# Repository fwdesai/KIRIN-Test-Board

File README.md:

Test board for the KIRIN hardware accelerator which was developed by Bo Wun Cheng.

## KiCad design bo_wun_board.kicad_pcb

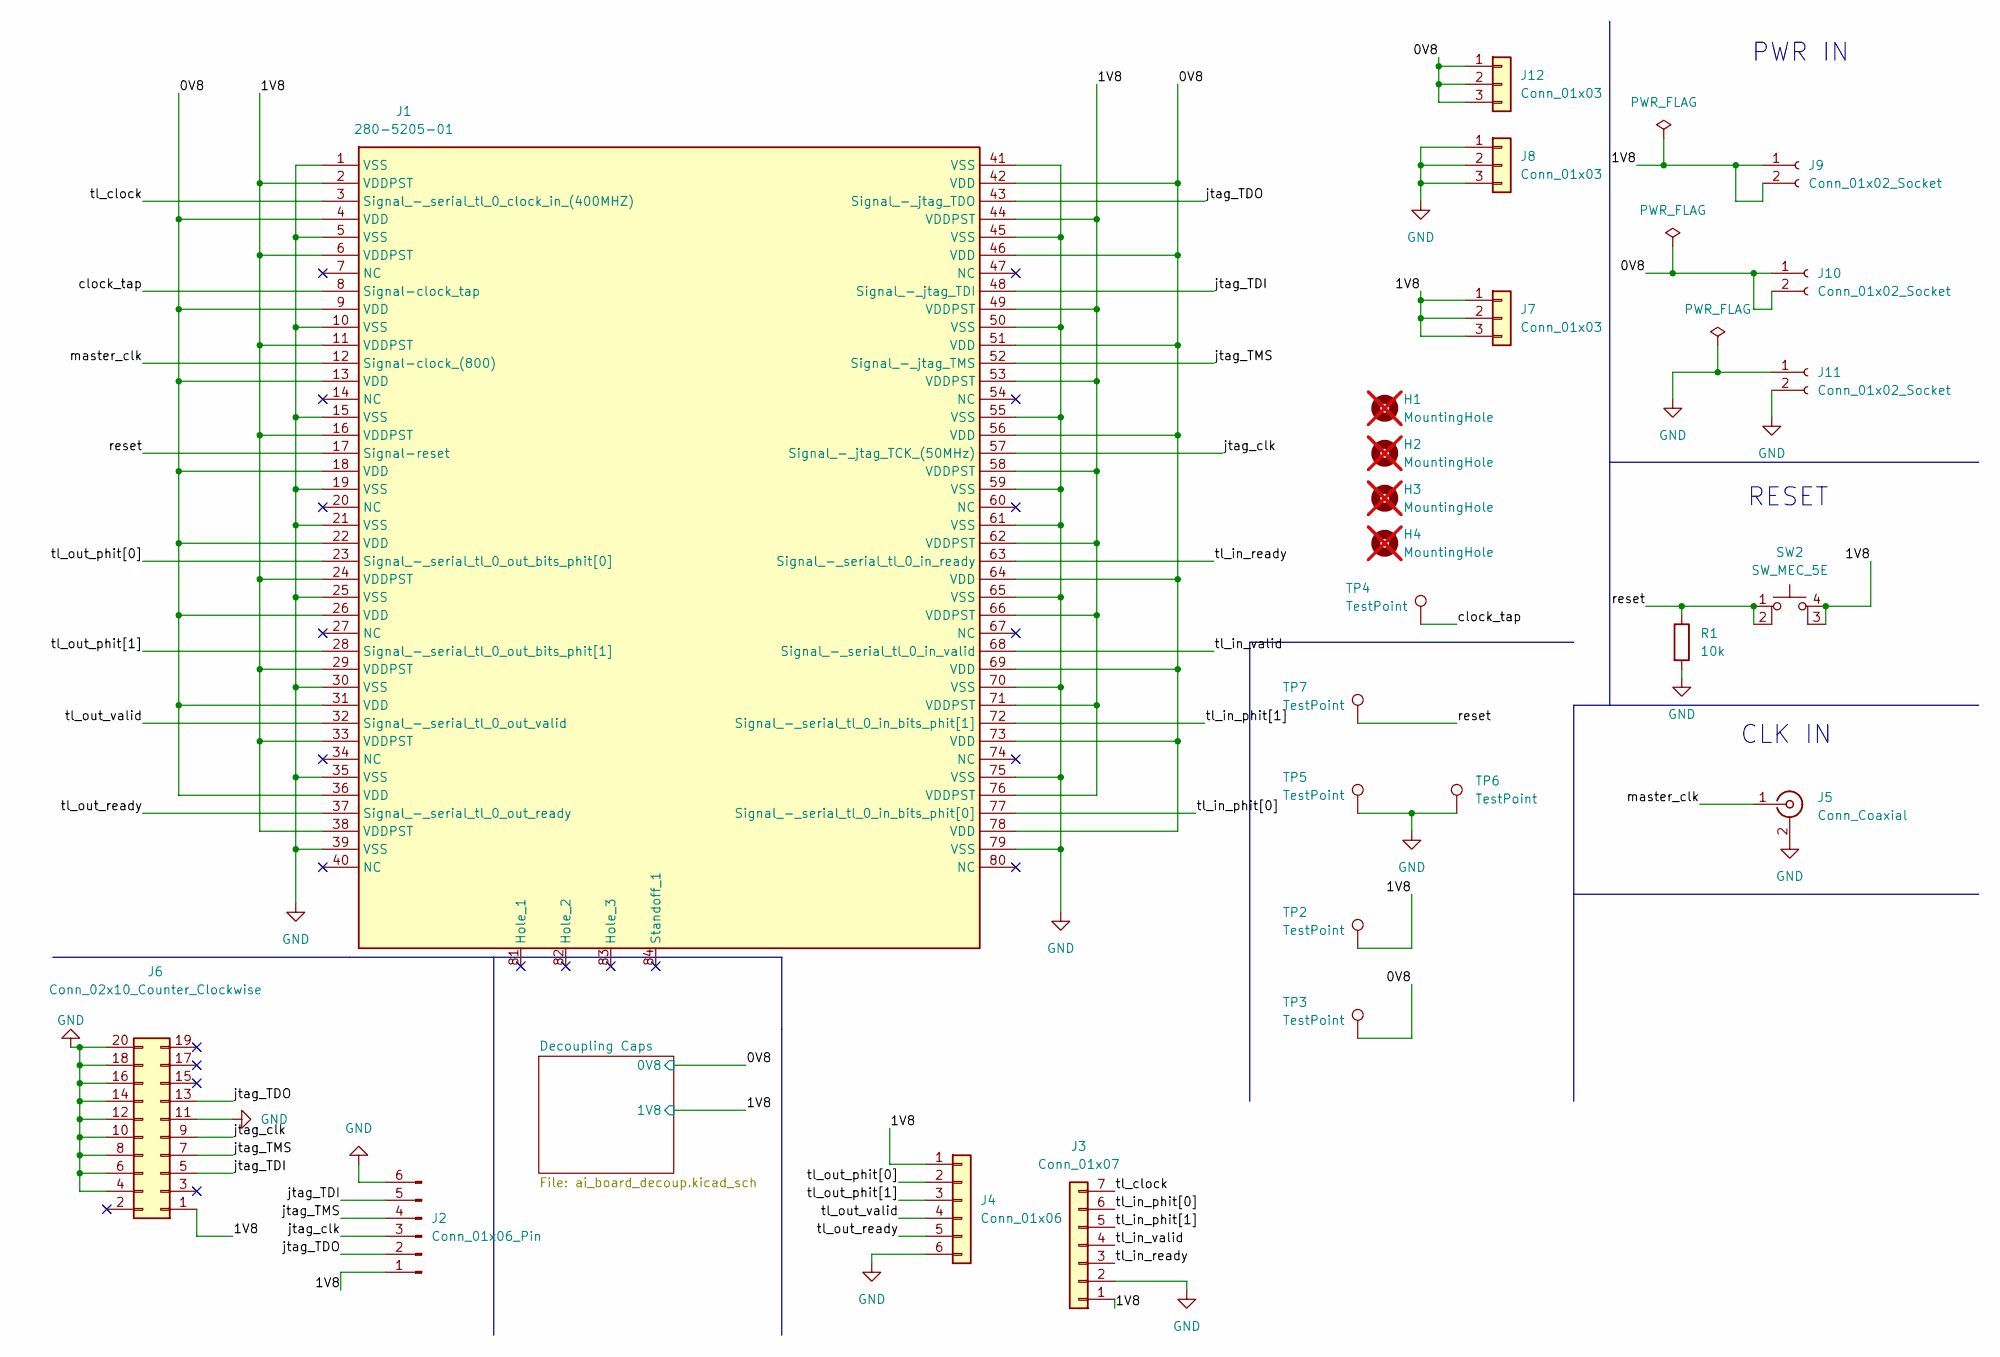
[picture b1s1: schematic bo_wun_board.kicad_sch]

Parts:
H1, H2, H3, H4: MountingHole; MountingHole_5.3mm_M5; not fitted
J1: 280-5205-01; chip_socket_new; Mouser Part Number 517-280-5205-01
J2: Conn_01x06_Pin; PinHeader_1x06_P2.54mm_Vertical; LCSC Part # C5156615
J3: Conn_01x07; PinHeader_1x07_P2.54mm_Vertical; LCSC Part # C5360900
J4: Conn_01x06; PinHeader_1x06_P2.54mm_Vertical; LCSC Part # C5156615
J5: Conn_Coaxial; SMA_Amphenol_132134-16_Vertical; LCSC Part # C2987686
J6: Conn_02x10_Counter_Clockwise; smd_jtag_connector
J7, J8, J12: Conn_01x03; PinHeader_1x03_P2.54mm_Vertical; LCSC Part # C5360899
J9: Conn_01x02_Socket; CONN_24.243_MTC; LCSC Part # C7437323
J10: Conn_01x02_Socket; CONN_24.243_MTC; LCSC Part # C7437321
J11: Conn_01x02_Socket; CONN_24.243_MTC; LCSC Part # C7437322
R1: 10k; R_0402_1005Metric; LCSC Part # C25744
SW2: SW_MEC_5E; teco_push_button; LCSC Part # C428628
TP2: TestPoint; TestPoint_Keystone_5010-5014_Multipurpose; LCSC Part # C238128
TP3: TestPoint; TestPoint_Keystone_5010-5014_Multipurpose; LCSC Part # C2906765
TP4: TestPoint; TestPoint_Keystone_5010-5014_Multipurpose; LCSC Part # C2906767
TP5, TP6: TestPoint; TestPoint_Keystone_5010-5014_Multipurpose; LCSC Part # C238127
TP7: TestPoint; TestPoint_Keystone_5010-5014_Multipurpose; LCSC Part # C2906766

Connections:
/0V8: J1.4 (VDD), J1.9 (VDD), J1.13 (VDD), J1.18 (VDD), J1.22 (VDD), J1.26 (VDD), J1.31 (VDD), J1.36 (VDD), J1.42 (VDD), J1.46 (VDD), J1.51 (VDD), J1.56 (VDD), J1.64 (VDD), J1.69 (VDD), J1.73 (VDD), J1.78 (VDD), J10.1, J10.2, J12.1, J12.2, J12.3, TP3.1 (1_1); also elsewhere on the board
/1V8: J1.2 (VDDPST), J1.6 (VDDPST), J1.11 (VDDPST), J1.16 (VDDPST), J1.24 (VDDPST), J1.29 (VDDPST), J1.33 (VDDPST), J1.38 (VDDPST), J1.44 (VDDPST), J1.49 (VDDPST), J1.53 (VDDPST), J1.58 (VDDPST), J1.62 (VDDPST), J1.66 (VDDPST), J1.71 (VDDPST), J1.76 (VDDPST), J2.1, J3.1, J4.1, J6.1, J7.1, J7.2, J7.3, J9.1, J9.2, SW2.3 (K), SW2.4 (A), TP2.1 (1_1); also elsewhere on the board
/clock_tap: J1.8 (Signal-clock_tap), TP4.1 (1_1)
/jtag_TDI: J1.48 (Signal_-_jtag_TDI), J2.5, J6.5 (Pin_3)
/jtag_TDO: J1.43 (Signal_-_jtag_TDO), J2.2, J6.13 (Pin_7)
/jtag_TMS: J1.52 (Signal_-_jtag_TMS), J2.4, J6.7 (Pin_4)
/jtag_clk: J1.57 (Signal_-_jtag_TCK_(50MHz)), J2.3, J6.9 (Pin_5)
/master_clk: J1.12 (Signal-clock_(800)), J5.1 (In)
/reset: J1.17 (Signal-reset), R1.1, SW2.1, SW2.2, TP7.1 (1_1)
/tl_clock: J1.3 (Signal_-_serial_tl_0_clock_in_(400MHZ)), J3.7
/tl_in_phit[0]: J1.77 (Signal_-_serial_tl_0_in_bits_phit[0]), J3.6
/tl_in_phit[1]: J1.72 (Signal_-_serial_tl_0_in_bits_phit[1]), J3.5
/tl_in_ready: J1.63 (Signal_-_serial_tl_0_in_ready), J3.3
/tl_in_valid: J1.68 (Signal_-_serial_tl_0_in_valid), J3.4
/tl_out_phit[0]: J1.23 (Signal_-_serial_tl_0_out_bits_phit[0]), J4.2
/tl_out_phit[1]: J1.28 (Signal_-_serial_tl_0_out_bits_phit[1]), J4.3
/tl_out_ready: J1.37 (Signal_-_serial_tl_0_out_ready), J4.5
/tl_out_valid: J1.32 (Signal_-_serial_tl_0_out_valid), J4.4
GND: J1.1 (VSS), J1.5 (VSS), J1.10 (VSS), J1.15 (VSS), J1.19 (VSS), J1.21 (VSS), J1.25 (VSS), J1.30 (VSS), J1.35 (VSS), J1.39 (VSS), J1.41 (VSS), J1.45 (VSS), J1.50 (VSS), J1.55 (VSS), J1.59 (VSS), J1.61 (VSS), J1.65 (VSS), J1.70 (VSS), J1.75 (VSS), J1.79 (VSS), J2.6, J3.2, J4.6, J5.2 (Ext), J6.4 (Pin_19), J6.6 (Pin_18), J6.8 (Pin_17), J6.10 (Pin_16), J6.11 (Pin_6), J6.12 (Pin_15), J6.14, J6.16 (Pin_13), J6.18 (Pin_12), J6.20 (Pin_11), J8.1, J8.2, J8.3, J11.1, J11.2, R1.2, TP5.1 (1_1), TP6.1 (1_1); also elsewhere on the board

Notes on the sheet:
PWR IN
CLK IN
RESET

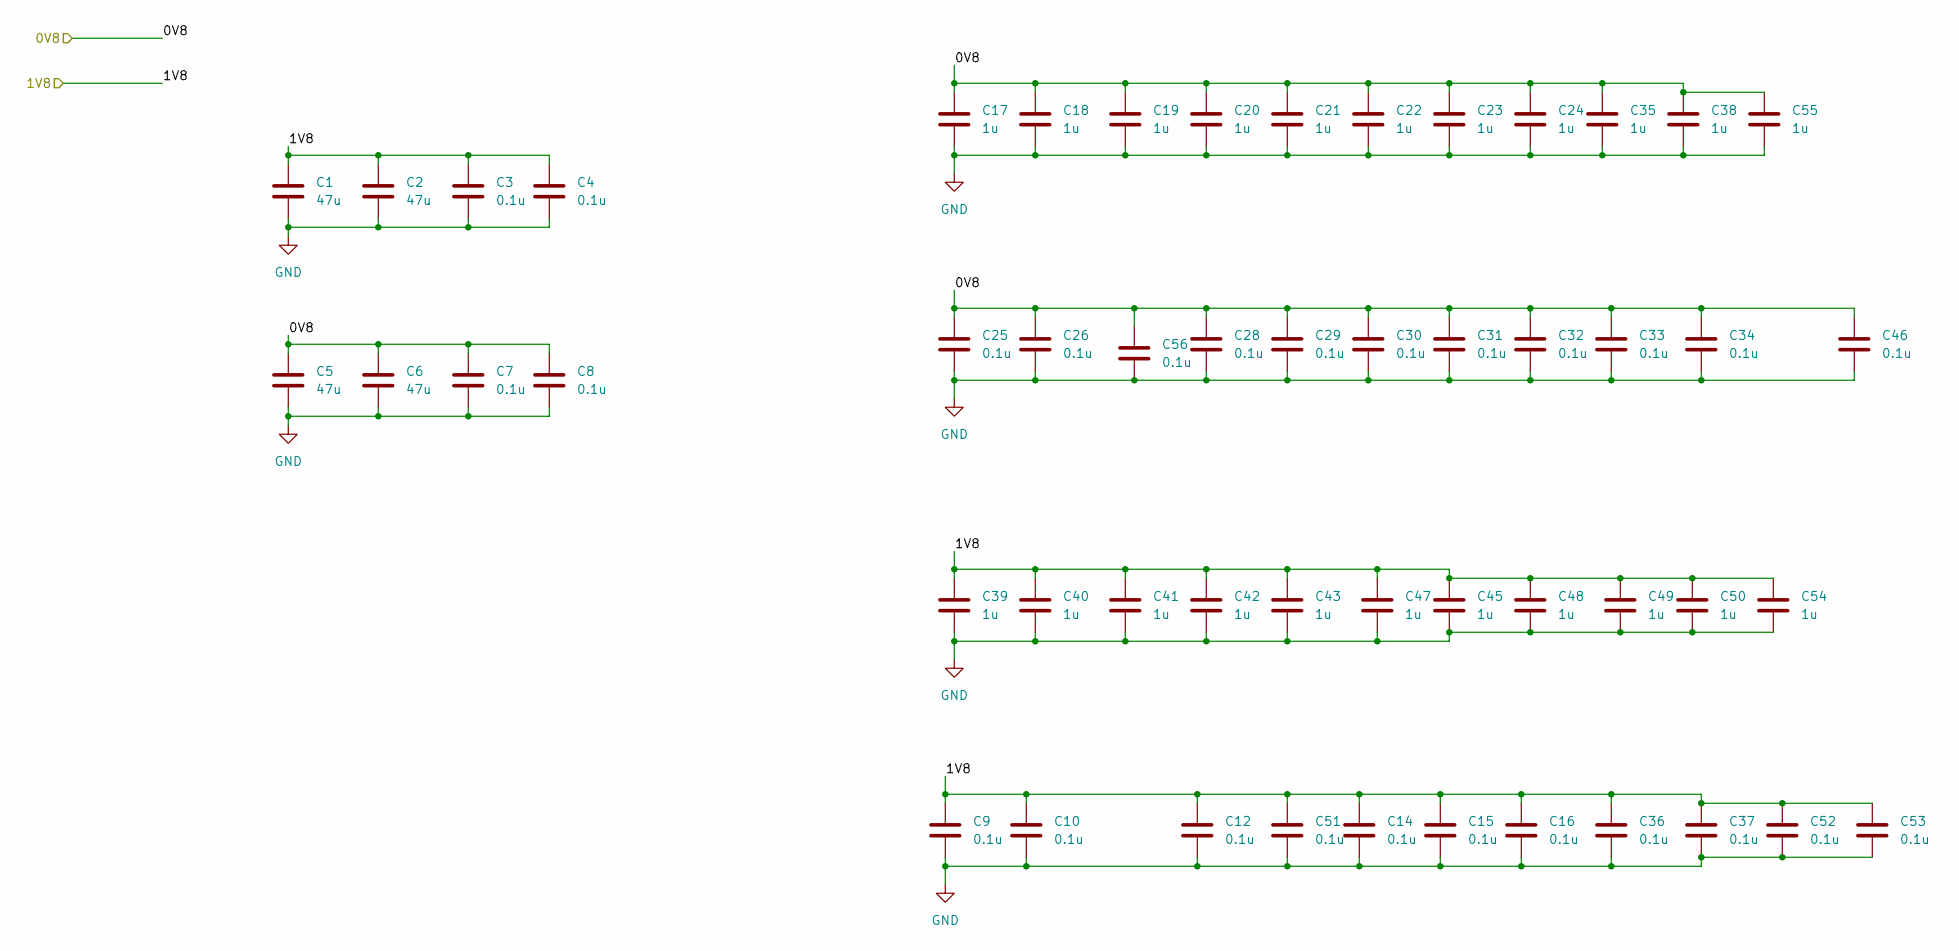
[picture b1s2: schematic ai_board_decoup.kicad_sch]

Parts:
C1, C2, C5, C6: 47u; C_0805_2012Metric; LCSC C16780
C3, C4, C7, C8, C9, C10, C12, C14, C15, C16, C25, C26, C28, C29, C30, C31, C32, C33, C34, C36, C37, C46, C51, C52, C53, C56: 0.1u; C_0402_1005Metric; LCSC C1525
C17, C18, C19, C20, C21, C22, C23, C24, C35, C38, C39, C40, C41, C42, C43, C45, C47, C48, C49, C50, C54, C55: 1u; C_0805_2012Metric; LCSC C28323

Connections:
/0V8: C5.1, C6.1, C7.1, C8.1, C17.1, C18.1, C19.1, C20.1, C21.1, C22.1, C23.1, C24.1, C25.1, C26.1, C28.1, C29.1, C30.1, C31.1, C32.1, C33.1, C34.1, C35.1, C38.1, C46.1, C55.1, C56.1; also elsewhere on the board
/1V8: C1.1, C2.1, C3.1, C4.1, C9.1, C10.1, C12.1, C14.1, C15.1, C16.1, C36.1, C37.1, C39.1, C40.1, C41.1, C42.1, C43.1, C45.1, C47.1, C48.1, C49.1, C50.1, C51.1, C52.1, C53.1, C54.1; also elsewhere on the board
GND: C1.2, C2.2, C3.2, C4.2, C5.2, C6.2, C7.2, C8.2, C9.2, C10.2, C12.2, C14.2, C15.2, C16.2, C17.2, C18.2, C19.2, C20.2, C21.2, C22.2, C23.2, C24.2, C25.2, C26.2, C28.2, C29.2, C30.2, C31.2, C32.2, C33.2, C34.2, C35.2, C36.2, C37.2, C38.2, C39.2, C40.2, C41.2, C42.2, C43.2, C45.2, C46.2, C47.2, C48.2, C49.2, C50.2, C51.2, C52.2, C53.2, C54.2, C55.2, C56.2; also elsewhere on the board

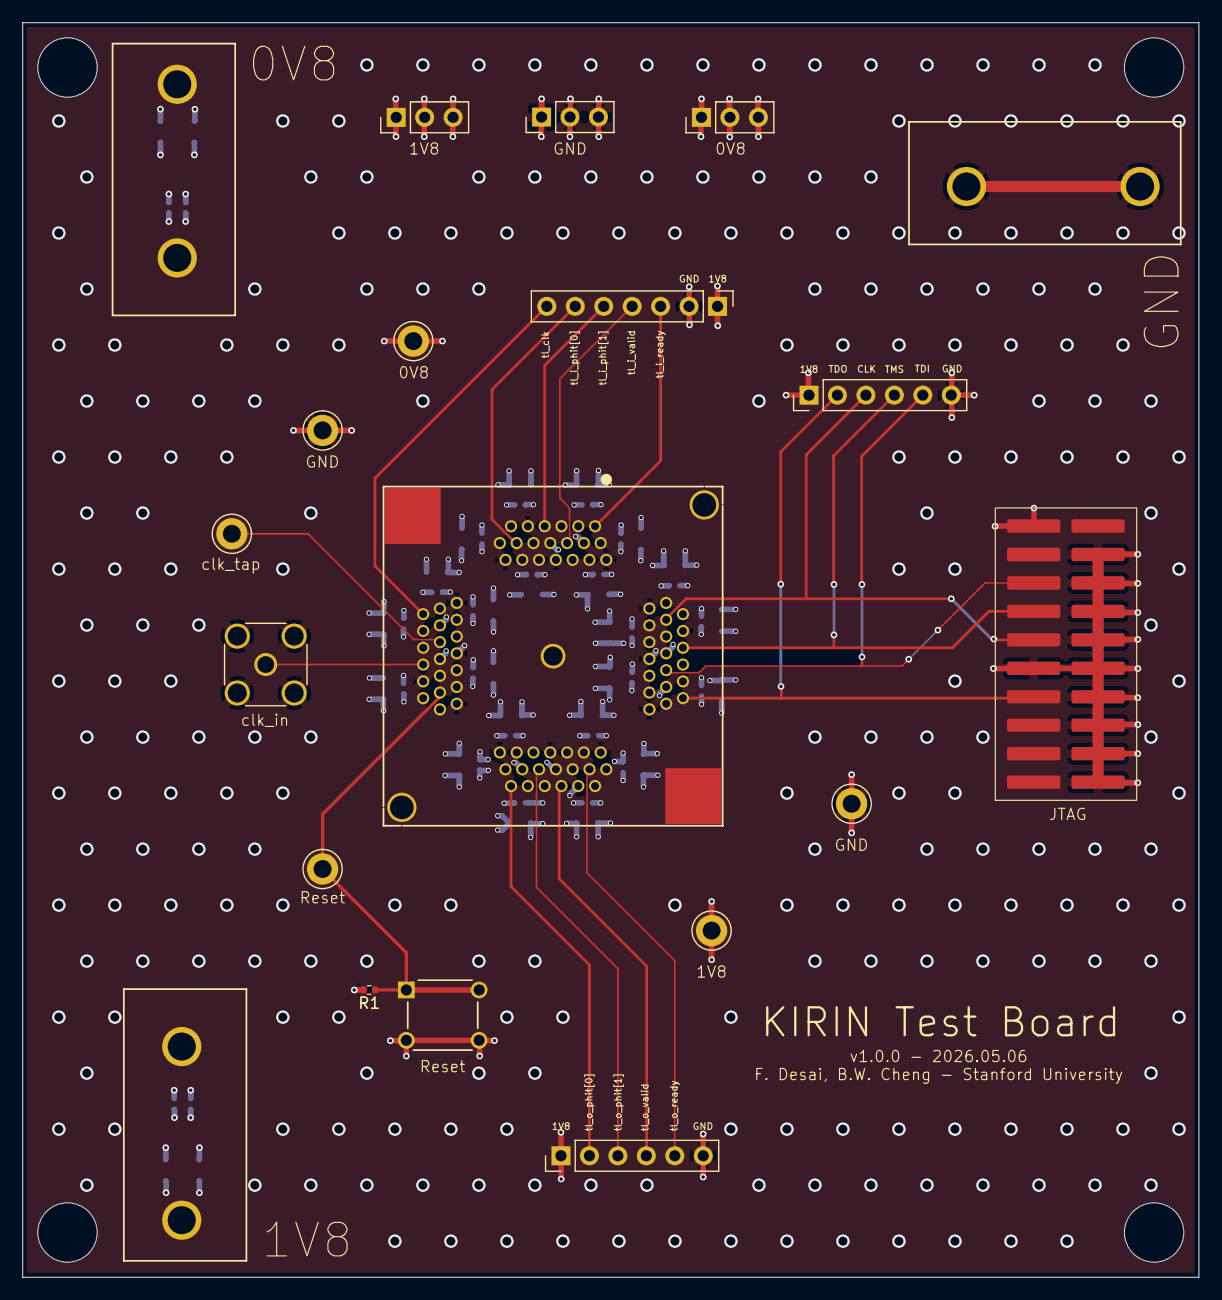
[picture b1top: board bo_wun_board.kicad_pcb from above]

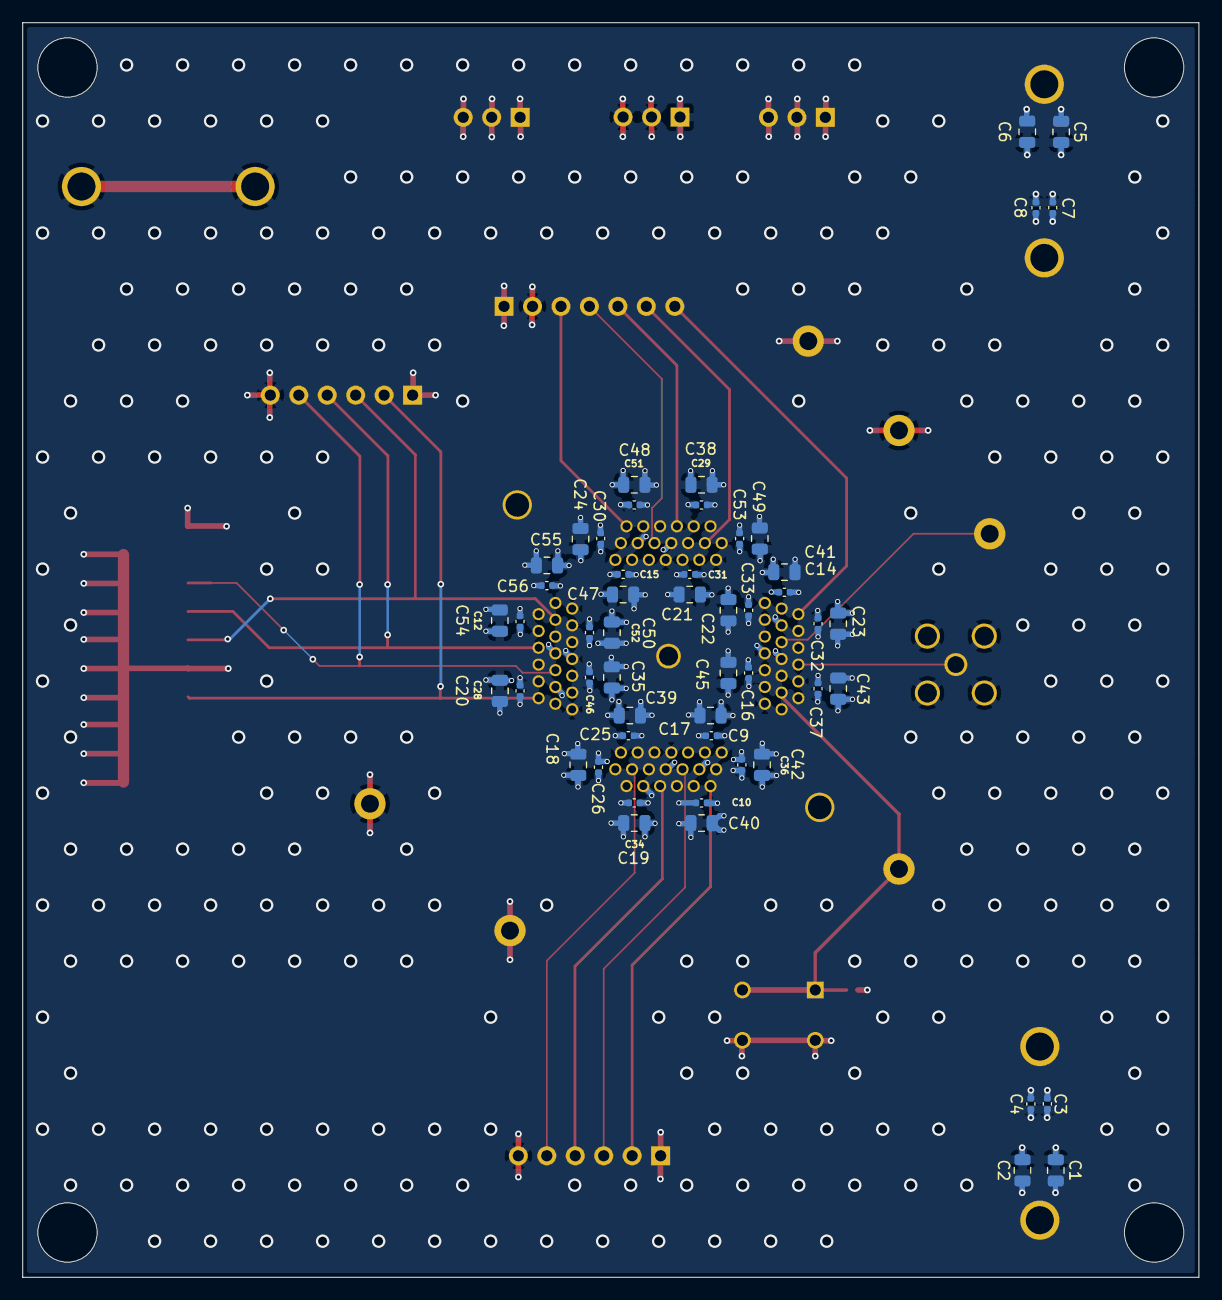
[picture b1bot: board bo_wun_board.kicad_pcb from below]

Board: 6 copper layers, 105.0 x 112.0 mm, 76 parts (52 on the bottom side), 19 nets.
